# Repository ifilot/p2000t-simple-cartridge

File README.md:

# P2000T Simple Cartridge

## Purpose

This repository contains a simple example on how to build your own cartridge
for the P2000T.

For more information, see [this blog post](https://www.philips-p2000t.nl/cartridges/basic-cartridge).

## Contents

* [KiCad source files](pcb/basic_cartridge) for the PCB.
* [STL files]((case)) for a cartridge enclosure.
* [Simple Hello World program](assembly/hello_world/hello_world.asm) source code for the ROM.

## Cartridge BOM

* [74HC00 Quad NAND gate](https://www.reichelt.nl/nl/nl/4-voudige-2-input-nand-poorten-2--6-v-dil-14-74hc-00-p3119.html?r=1)
* [SST39SF010 rom chip](https://www.reichelt.nl/nl/nl/multi-nor-flash-geheugen-1-mb-128-k-x-8-5-v-plcc-32-39sf01070-4c-n-p266390.html?r=1)
* [PLCC32 IC-socket](https://www.reichelt.nl/nl/nl/ic-fitting-32-polig-plcc-plcc-32-p14700.html?r=1)
* 2x 0.1 uF capacitor

## Building the software

Compile the assembly file via:

```bash
cd assembly
make
```

and flash the resulting `hello_world.bin` file to the EEPROM. 

See also [this repository](https://github.com/ifilot/pico-sst39sf0x0-programmer) 
for a cheap PICO-based SST39SF0x0 flasher.

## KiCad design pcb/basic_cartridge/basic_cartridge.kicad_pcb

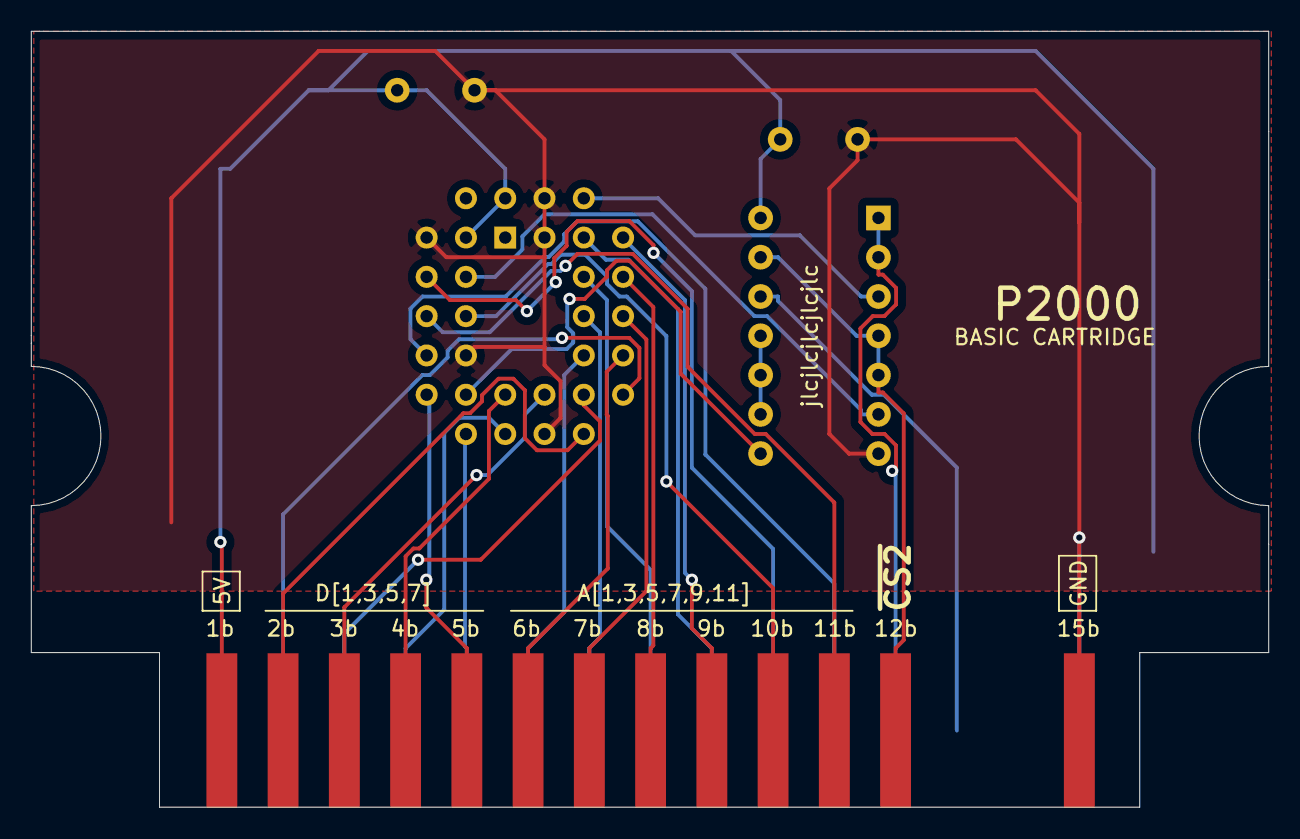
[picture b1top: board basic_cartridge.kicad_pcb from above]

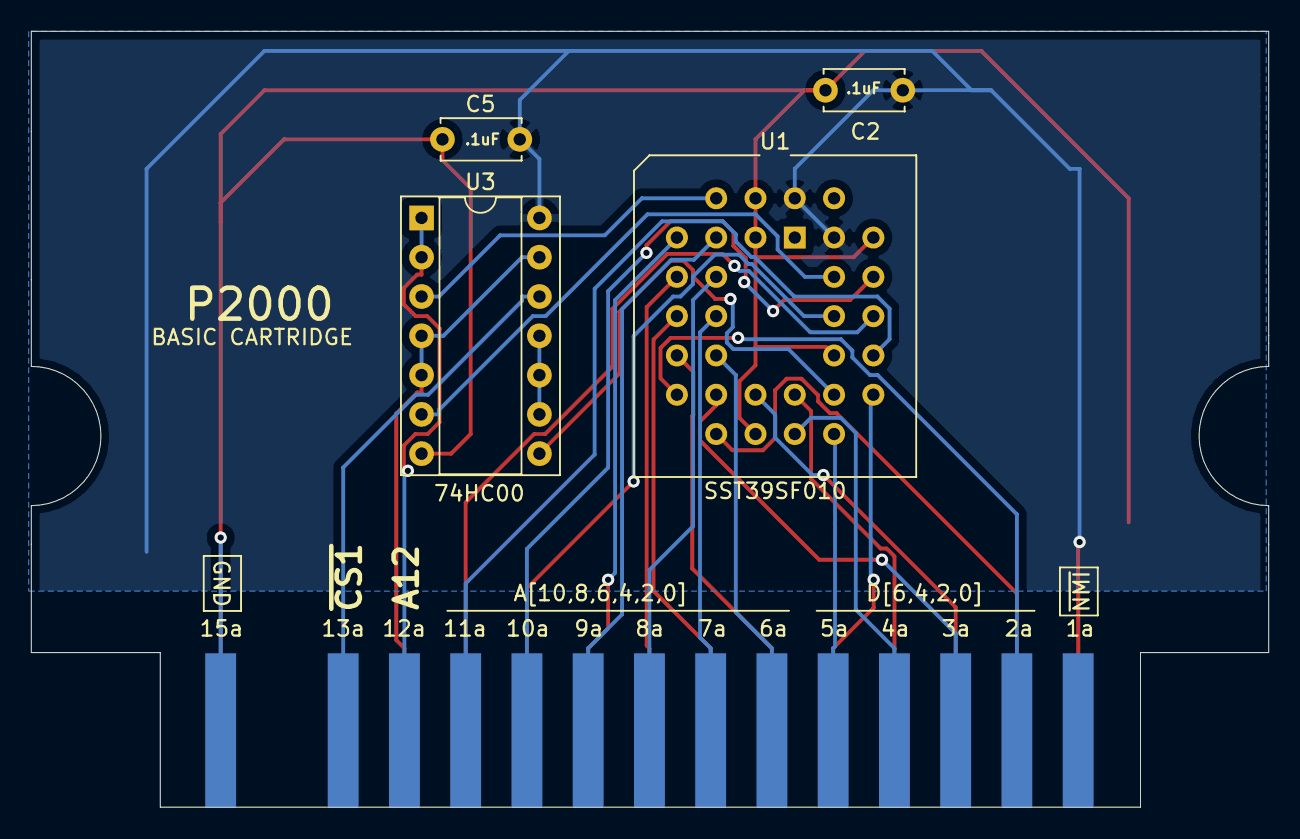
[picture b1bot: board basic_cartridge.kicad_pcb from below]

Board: 2 copper layers, 80.0 x 50.2 mm, 5 parts (5 on the bottom side), 29 nets.

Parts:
C2, C5: .1uF; C_Disc_D5.0mm_W2.5mm_P5.00mm
J1: P2000T_cartridge_edge; p2000t_cartridge_edge
U1: SST39SF010; PLCC-32_THT-Socket
U3: 74HC00; DIP-14_W7.62mm_Socket

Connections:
+5V: C2.1, C5.1, J1.1b, U1.31 (PGM), U1.32 (VCC), U3.14 (VCC)
A0: J1.6a, U1.12 (A0)
A1: J1.6b, U1.11 (A1)
A2: J1.7a, U1.10 (A2)
A3: J1.7b, U1.9 (A3)
A4: J1.8a, U1.8 (A4)
A5: J1.8b, U1.7 (A5)
A6: J1.9a, U1.6 (A6)
A7: J1.9b, U1.5 (A7)
A8: J1.10a, U1.27 (A8)
A9: J1.10b, U1.26 (A9)
A10: J1.11a, U1.23 (A10)
A11: J1.11b, U1.25 (A11)
A12: U1.4 (A12), U3.3
A12C: J1.12a, U3.1, U3.2
A13: U1.28 (A13), U3.6
D0: J1.2a, U1.13 (D0)
D1: J1.2b, U1.14 (D1)
D2: J1.3a, U1.15 (D2)
D3: J1.3b, U1.17 (D3)
D4: J1.4a, U1.18 (D4)
D5: J1.4b, U1.19 (D5)
D6: J1.5a, U1.20 (D6)
D7: J1.5b, U1.21 (D7)
GND: C2.2, C5.2, J1.15a, J1.15b, U1.2 (A16), U1.3 (A15), U1.16 (GND), U1.24 (OE), U1.29 (A14), U3.7 (GND)
unnamed: U3.9, U3.10, U3.11
~CARSEL1: J1.13a, U3.12
~CARSEL2: J1.12b, U3.4, U3.5, U3.13
~CS: U1.22 (CE), U3.8

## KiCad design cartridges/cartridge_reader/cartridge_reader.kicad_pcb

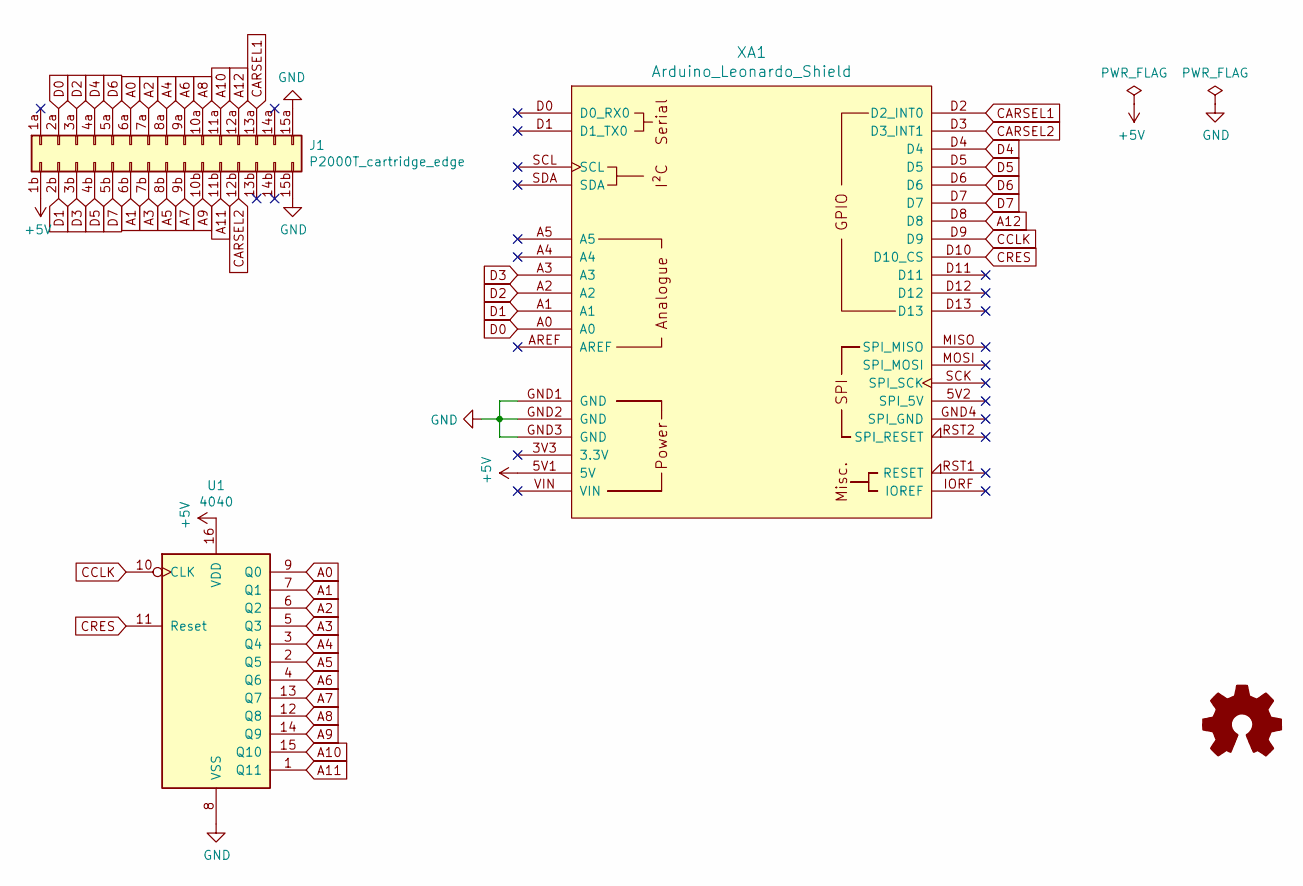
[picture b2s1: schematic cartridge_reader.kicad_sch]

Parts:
J1: P2000T_cartridge_edge; EdgeConnector2x15_no_screws
U1: 4040; DIP-16_W7.62mm_Socket
XA1: Arduino_Leonardo_Shield; Arduino_Uno_Shield

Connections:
+5V: J1.1b, U1.16 (VDD), XA1.5V1 (5V)
A0: J1.6a, U1.9 (Q0)
A1: J1.6b, U1.7 (Q1)
A2: J1.7a, U1.6 (Q2)
A3: J1.7b, U1.5 (Q3)
A4: J1.8a, U1.3 (Q4)
A5: J1.8b, U1.2 (Q5)
A6: J1.9a, U1.4 (Q6)
A7: J1.9b, U1.13 (Q7)
A8: J1.10a, U1.12 (Q8)
A9: J1.10b, U1.14 (Q9)
A10: J1.11a, U1.15 (Q10)
A11: J1.11b, U1.1 (Q11)
A12: J1.12a, XA1.D8
CARSEL1: J1.13a, XA1.D2 (D2_INT0)
CARSEL2: J1.12b, XA1.D3 (D3_INT1)
CCLK: U1.10 (CLK), XA1.D9
CRES: U1.11 (Reset), XA1.D10 (D10_CS)
D0: J1.2a, XA1.A0
D1: J1.2b, XA1.A1
D2: J1.3a, XA1.A2
D3: J1.3b, XA1.A3
D4: J1.4a, XA1.D4
D5: J1.4b, XA1.D5
D6: J1.5a, XA1.D6
D7: J1.5b, XA1.D7
GND: J1.15a, J1.15b, U1.8 (VSS), XA1.GND1 (GND), XA1.GND2 (GND), XA1.GND3 (GND)

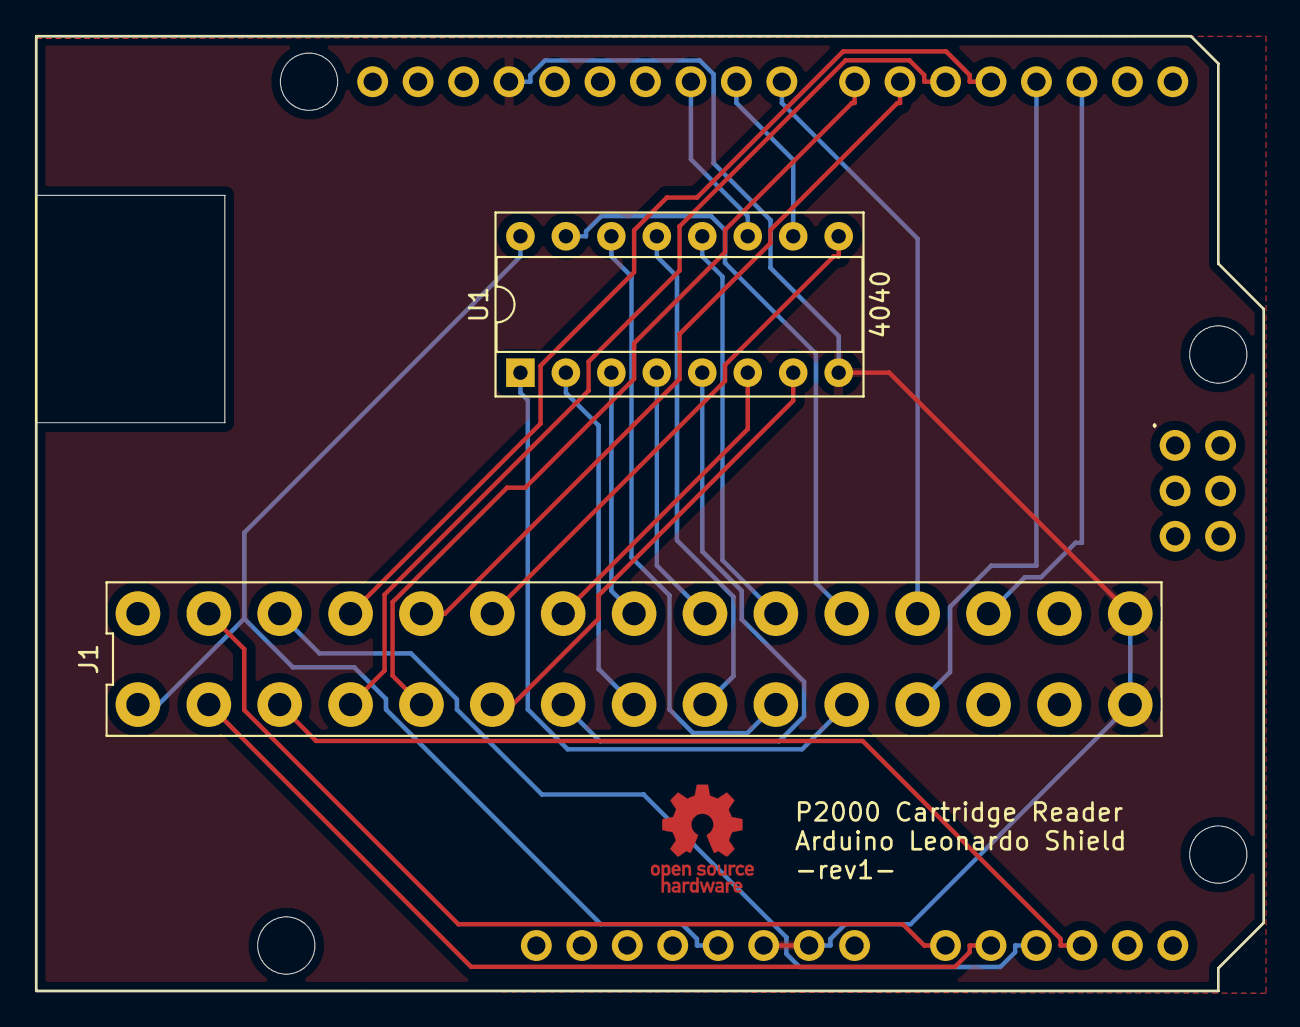
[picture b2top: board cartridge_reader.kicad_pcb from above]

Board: 2 copper layers, 68.6 x 53.3 mm, 3 parts (0 on the bottom side), 27 nets.

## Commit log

2023-02-19 Initial commit of basic cartridge
2023-02-20 Adding cartridge reader
2023-02-20 Making small adjustments to lay-out
2023-08-05 Refactoring repository
2023-08-05 Adding autocompilation
2023-08-05 Fixing badges
2023-08-05 Updating README.md
2025-10-19 Enhance comments in hello_world.asm - issue #1
    Added comments explaining byte count and checksum fields.
2025-10-19 Update build workflow with new action versions
    Updated GitHub Actions workflow to use newer action versions and improved dependency installation command.

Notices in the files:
README.md:
License: GPL v3
